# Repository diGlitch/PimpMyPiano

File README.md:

# PimpMyPiano
## Mbed based interface between Fatar TP44GH keybed and the midi world
---------------------------------------------------------------------------------------------------
Some day the controller board of my StudioLogic SL990Pro stopped working. Instead of buying a whole new masterkeybard I though "why not building one my self and reusing the high quality Fata TP44GH keybed in there". What had to be done was to read out the double button matrix (two buttons/sensors for each note), meassuring the time between two button presses and convert this data into midi commands after about a year I ended up with a Mbed based interface between a Fatar TP44GH keybed and the midi world.

## How to make it work || Underconstruction
These instructions will get you a copy of the project up and running on your local machine for development and testing purposes. See deployment for notes on how to deploy the project on a live system.

There are two parts: The software and the hardware.

### Prerequisites || Underconstruction
What things you need to install the software and how to install them

You will need ...:
* an ARM MBED ready board. I used the [NUCLEO-F411RE](https://os.mbed.com/platforms/ST-Nucleo-F411RE/) from ST. I guess the 100Mhz are a bit overkill so assume that something slower with similar pinout would do.
* hardware that connects the Nucleo with the Button Matrix of the piano. See Hardware folder for schematic and other hardware related details such as a part list.
* software that runs on the Nucleo. You can find the [PlatformIO](http://platformio.org) project in the src folder. Just clone the repo or download scr folder as ZIP and open "PimpMyPiano" folder in platformIO.

## Build With
* [MBED OS](https://www.mbed.com/en/platform/mbed-os/)
* [PlatformIO](http://platformio.org) extension for [VSCode](https://code.visualstudio.com/)

## Contributing || Underconstruction

### What is there to be improved
* Overall code base in terms of speed

## Authors
* **Jeremy Constantin Börker** - *Initial and so far all the work* - [diGlitch](https://github.com/diGlitch)

## License
This project is licensed under the GNU General Public License v3.0 - see the [LICENSE](LICENSE) file for details

## Acknowledgments
* Francois Best's Mbed MIDI Library for Arduino ported by Hiroshi Suga
* YoongHM's Mbed shift register library
* Processing for the mapping formular

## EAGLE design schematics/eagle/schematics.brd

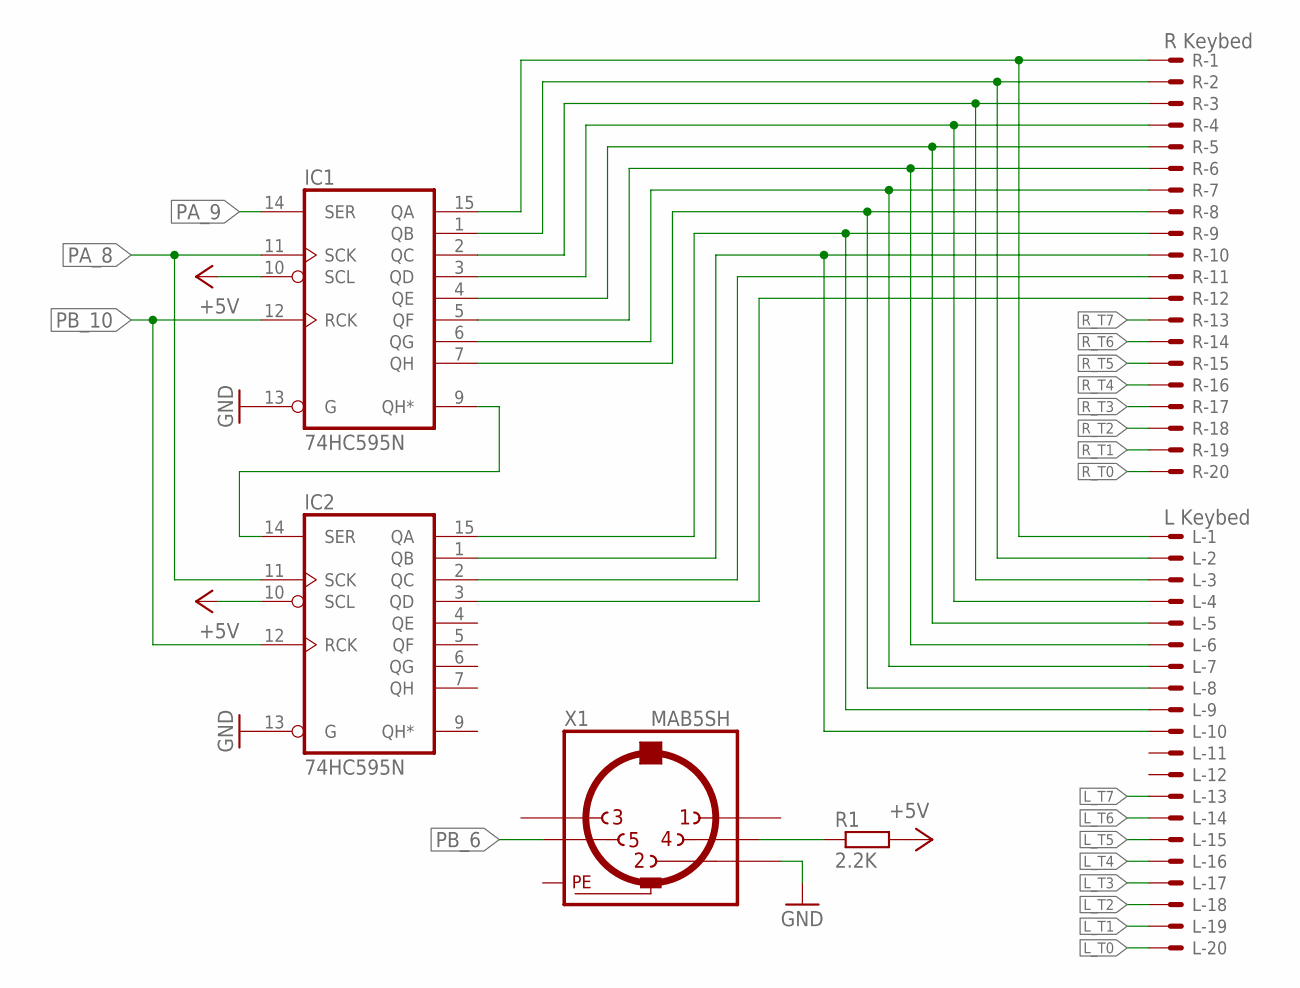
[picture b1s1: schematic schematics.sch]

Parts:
IC1, IC2: 74HC595N; DIL16
L: L Keybed; 5566-20
R: R Keybed; 5566-20
R1: 2.2K; 0207/10
X1: MAB5SH

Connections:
+5V: IC1.10 (SCL), IC2.10 (SCL), R1.2
GND: IC1.8 (GND), IC1.13 (G), IC2.8 (GND), IC2.13 (G), X1.2
L_T0: L.20
L_T1: L.19
L_T2: L.18
L_T3: L.17
L_T4: L.16
L_T5: L.15
L_T6: L.14
L_T7: L.13
unnamed: IC1.15 (QA), L.1, R.1
unnamed: IC1.1 (QB), L.2, R.2
unnamed: IC1.2 (QC), L.3, R.3
unnamed: IC1.3 (QD), L.4, R.4
unnamed: IC1.4 (QE), L.5, R.5
unnamed: IC1.5 (QF), L.6, R.6
unnamed: IC1.6 (QG), L.7, R.7
unnamed: IC1.7 (QH), L.8, R.8
unnamed: IC2.15 (QA), L.9, R.9
unnamed: IC2.1 (QB), L.10, R.10
unnamed: IC2.2 (QC), R.11
unnamed: IC2.3 (QD), R.12
unnamed: IC1.9 (QH*), IC2.14 (SER)
unnamed: R1.1, X1.4
PA_8: IC1.12 (RCK), IC2.12 (RCK)
PA_9: IC1.14 (SER)
PB_6: X1.5
PB_10: IC1.11 (SCK), IC2.11 (SCK)
PE: X1.PE, X1.PE@ (PE)
R_T0: R.20
R_T1: R.19
R_T2: R.18
R_T3: R.17
R_T4: R.16
R_T5: R.15
R_T6: R.14
R_T7: R.13
VCC: IC1.16 (VCC), IC2.16 (VCC)

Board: 2 copper layers, 6 parts (0 on the bottom side), 20 nets, no tracks yet.

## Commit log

2018-09-27 Updated content
2018-09-27 Updated README, Licenses and added some files
2018-09-27 Switch to PlatformIO
2018-09-27 Added VelocityDevNotebook
2018-09-27 Publishing
2018-10-01 Added new formula to generate velocity 4 and implemented it
2018-10-02 Added some stuff here and there
2018-10-04 Added sliders and changed layout of Velocity Curve Designer
2018-10-04 Renamed file
2018-10-04 added printing and comments in Velo designer, tested new Velocity curves
2018-11-05 Started with creating the circuit in eagle and fritzing
2018-11-23 First java velocity curve designer commit. VeloCurveDesigner 2000
2019-02-06 Added potentially outdated data as backup
2019-10-25 Updates in VScode envs
2019-10-25 LookUpTableGenerator python attempt
